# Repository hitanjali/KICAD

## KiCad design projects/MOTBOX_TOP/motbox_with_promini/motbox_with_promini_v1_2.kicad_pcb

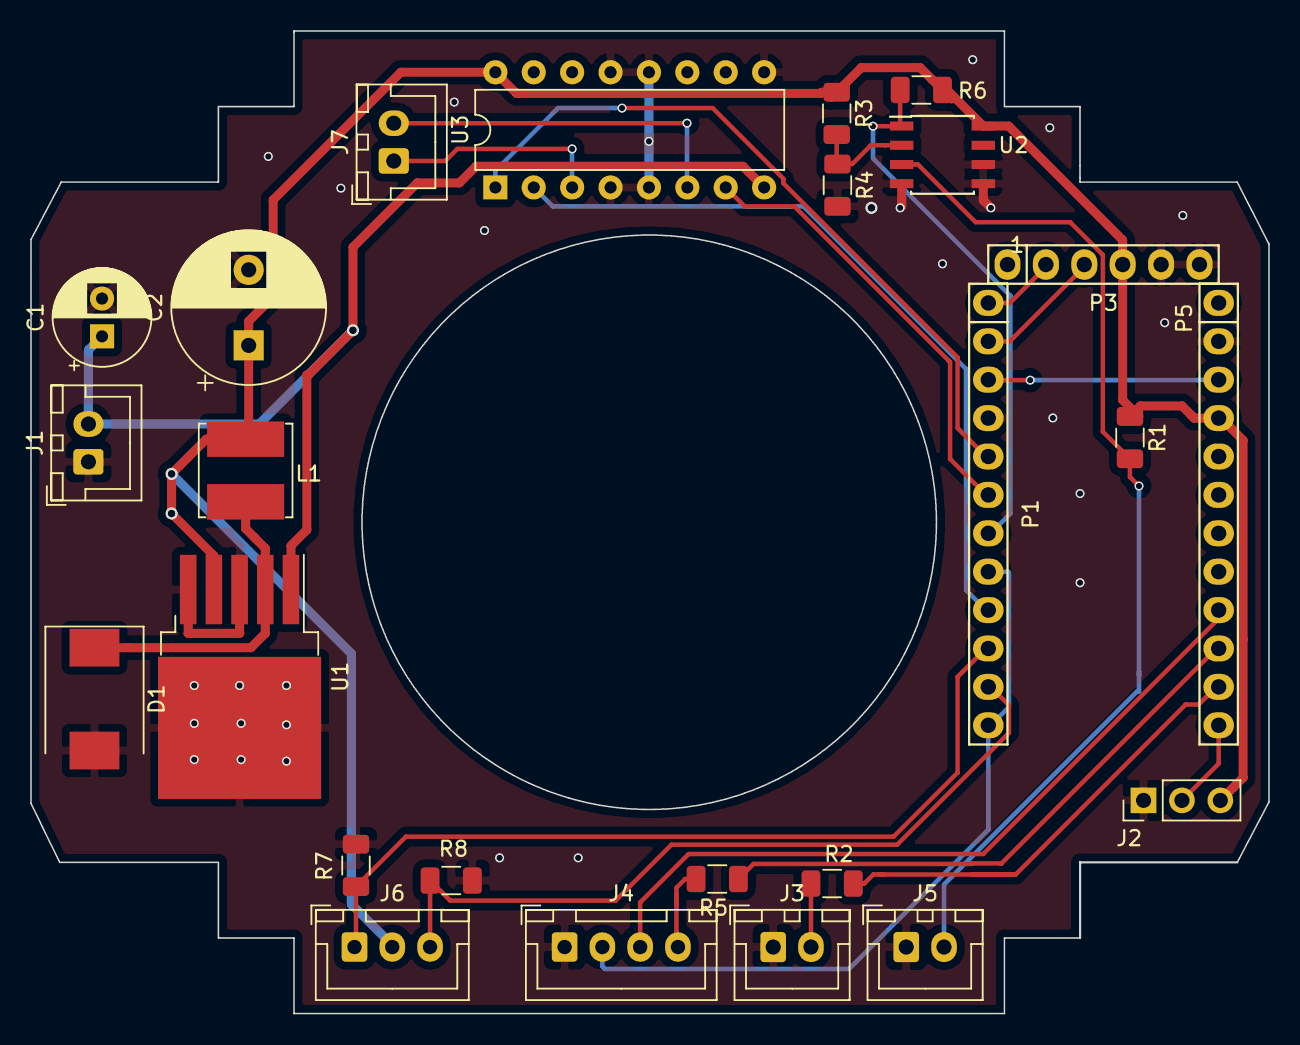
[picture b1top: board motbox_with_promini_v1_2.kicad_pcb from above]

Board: 2 copper layers, 81.9 x 65.0 mm, 25 parts (0 on the bottom side), 24 nets.

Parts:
C1: 100uF,25V; CP_Radial_D6.3mm_P2.50mm
C2: 1000uF,16V; CP_Radial_D10.0mm_P5.00mm
D1: SS34; D_SMC
J1, J3, J5, J7: JST_XH_2pin; JST_XH_B02B-XH-A_1x02_P2.50mm_Vertical
J2: Header_3pin_Male; PinHeader_1x03_P2.54mm_Vertical
J4: JST_XH_4pin; JST_XH_B04B-XH-A_1x04_P2.50mm_Vertical
J6: Conn_01x03; JST_XH_B03B-XH-A_1x03_P2.50mm_Vertical
L1: SRN6045-101M; L_Bourns_SRN6045TA
P1, P5: Female_Header_12pin; Socket_Strip_Arduino_1x12
P3: Female_Header_6pin; Socket_Strip_Arduino_1x06
R1: TBD; R_1206_3216Metric
R2, R5: 150; R_1206_3216Metric
R3, R4, R7, R8: 100K; R_1206_3216Metric
R6: 10K; R_1206_3216Metric
U1: LM2576R-5.0; TO-263-5_TabPin3
U2: LM393; SOIC-8_3.9x4.9mm_P1.27mm
U3: L293D; DIP-16_W7.62mm

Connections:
+5V: C2.1, J2.3, J6.2, L1.2, P3.4, P5.4, R1.1, R3.1, R6.1, U1.4, U2.8, U3.16
+12V: C1.1, J1.2, U1.1, U3.8
/0(Rx): P1.2, P3.3
/1(Tx): P1.1, P3.2
/2: P1.5, U3.1
/3: P1.6, U3.7
/4: P1.7, R6.2, U2.1
/5: J4.2, P1.8, P1.12
/6: P1.9, U3.2
/7: J6.1, P1.10, R7.1
/8: J6.3, P1.11, R8.1
/10: J2.2, P5.12
/11: P5.11, R2.1
/12: P5.10, R5.1
/13: J4.3, P5.9
/Reset: P1.3, P5.3
GND: C1.2, C2.2, D1.2, J1.1, J2.1, J3.1, J4.1, J5.1, P1.4, P3.5, P3.6, P5.2, R4.2, R7.2, R8.2, U1.3, U1.5, U2.4, U2.5, U2.6, U3.4, U3.5, U3.9, U3.12, U3.13
unnamed: D1.1, L1.1, U1.2
unnamed: J3.2, R2.2
unnamed: J4.4, R5.2
unnamed: J5.2, R1.2, U2.3
unnamed: J7.1, U3.3
unnamed: J7.2, U3.6
unnamed: R3.2, R4.1, U2.2

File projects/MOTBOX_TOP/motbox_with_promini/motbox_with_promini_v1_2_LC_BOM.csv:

S.No,Manufacturing Part No,Designator,Quantity,Description(VALUE),Package(CASE),Top/Bottom,Points (No. of Pins),Comments,,
1,  , "C1, " , "1" , "100uF,25V" , "Capacitor_THT:CP_Radial_D6.3mm_P2.50mm" , TOP , 2, "Polarized capacitor, small US symbol", , 
2,  , "C2, " , "1" , "1000uF,16V" , "Capacitor_THT:CP_Radial_D10.0mm_P5.00mm" , TOP , 2, "Polarized capacitor, small US symbol", , 
3,  , "D1, " , "1" , "SS34" , "Diode_SMD:D_SMC" , TOP , 2, "Schottky diode", , 
4,  , "J2, " , "1" , "Header_3pin_Male" , "Connector_PinHeader_2.54mm:PinHeader_1x03_P2.54mm_Vertical" , TOP , 3, "Generic connector, single row, 01x03, script generated (kicad-library-utils/schlib/autogen/connector/)", , 
5,  , "J4, " , "1" , "JST_XH_4pin" , "Connector_JST:JST_XH_B04B-XH-A_1x04_P2.50mm_Vertical" , TOP , 4, "Generic connector, single row, 01x04, script generated (kicad-library-utils/schlib/autogen/connector/)", , 
6,  , "J5, J7, J1, J3, " , "4" , "JST_XH_2pin" , "Connector_JST:JST_XH_B02B-XH-A_1x02_P2.50mm_Vertical" , TOP , 2, "Generic connector, single row, 01x02, script generated (kicad-library-utils/schlib/autogen/connector/)", , 
7,  , "J6, " , "1" , "JST_XH_3pin" , "Connector_JST:JST_XH_B03B-XH-A_1x03_P2.50mm_Vertical" , TOP , 3, "Generic connector, single row, 01x03, script generated (kicad-library-utils/schlib/autogen/connector/)", , 
8,  , "L1, " , "1" , "SRN6045-101M" , "Inductor_SMD:L_Bourns_SRN6045TA" , TOP , 2, "Inductor, small symbol", , 
9,  , "P1, P5, " , "2" , "Female_Header_12pin" , "Socket_Arduino_Pro_Mini:Socket_Strip_Arduino_1x12" , TOP , 12, "Generic connector, single row, 01x12, script generated (kicad-library-utils/schlib/autogen/connector/)", , 
10,  , "P3, " , "1" , "Female_Header_6pin" , "Socket_Arduino_Pro_Mini:Socket_Strip_Arduino_1x06" , TOP , 6, "Generic connector, single row, 01x06, script generated (kicad-library-utils/schlib/autogen/connector/)", , 
11,  , "R1, " , "1" , "60K" , "Resistor_SMD:R_1206_3216Metric" , TOP , 2, "Resistor, US symbol", , 
12,  , "R2, R5, " , "2" , "150R" , "Resistor_SMD:R_1206_3216Metric" , TOP , 2, "Resistor, US symbol", , 
13,  , "R3, R4, R8, R7, " , "4" , "100K" , "Resistor_SMD:R_1206_3216Metric" , TOP , 2, "Resistor, US symbol", , 
14,  , "R6, " , "1" , "10K" , "Resistor_SMD:R_1206_3216Metric" , TOP , 2, "Resistor, US symbol", , 
15,  , "U1, " , "1" , "LM2576R-5.0" , "Package_TO_SOT_SMD:TO-263-5_TabPin3" , TOP , 5, "12V, 3A SIMPLE SWITCHER® Step-Down Voltage Regulator, High Voltage Input, TO-263", , 
16,  , "U2, " , "1" , "LM393" , "Package_SO:SOIC-8_3.9x4.9mm_P1.27mm" , TOP , 8, "Low-Power, Low-Offset Voltage, Dual Comparators, DIP-8/SOIC-8/SSOP-8", , 
17,  , "U3, " , "1" , "L293D" , "Package_DIP:DIP-16_W7.62mm" , TOP , 16, "Quadruple Half-H Drivers", ,

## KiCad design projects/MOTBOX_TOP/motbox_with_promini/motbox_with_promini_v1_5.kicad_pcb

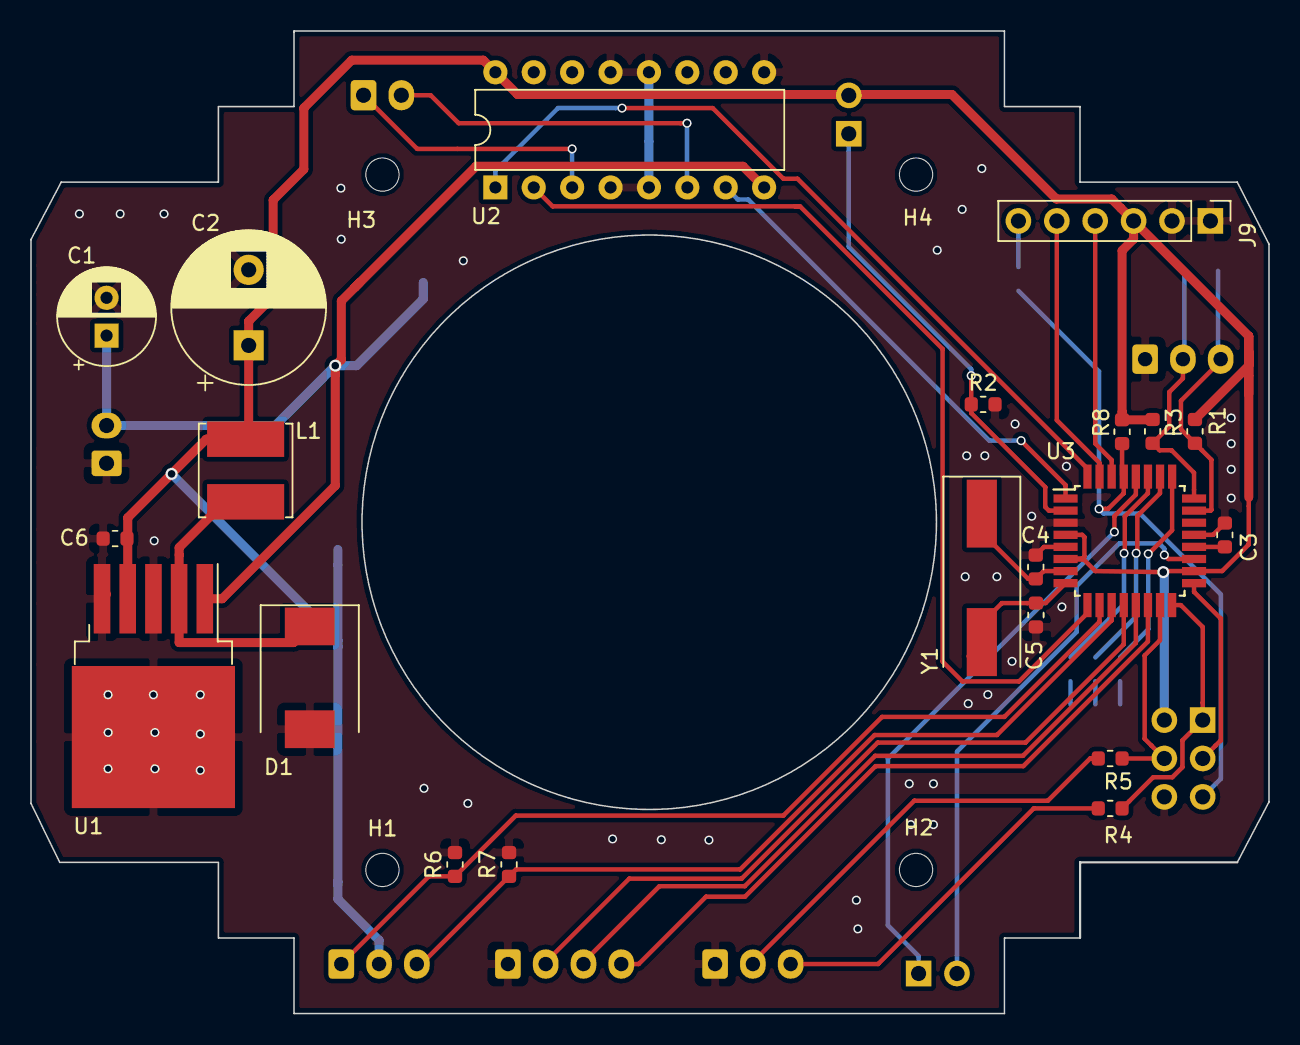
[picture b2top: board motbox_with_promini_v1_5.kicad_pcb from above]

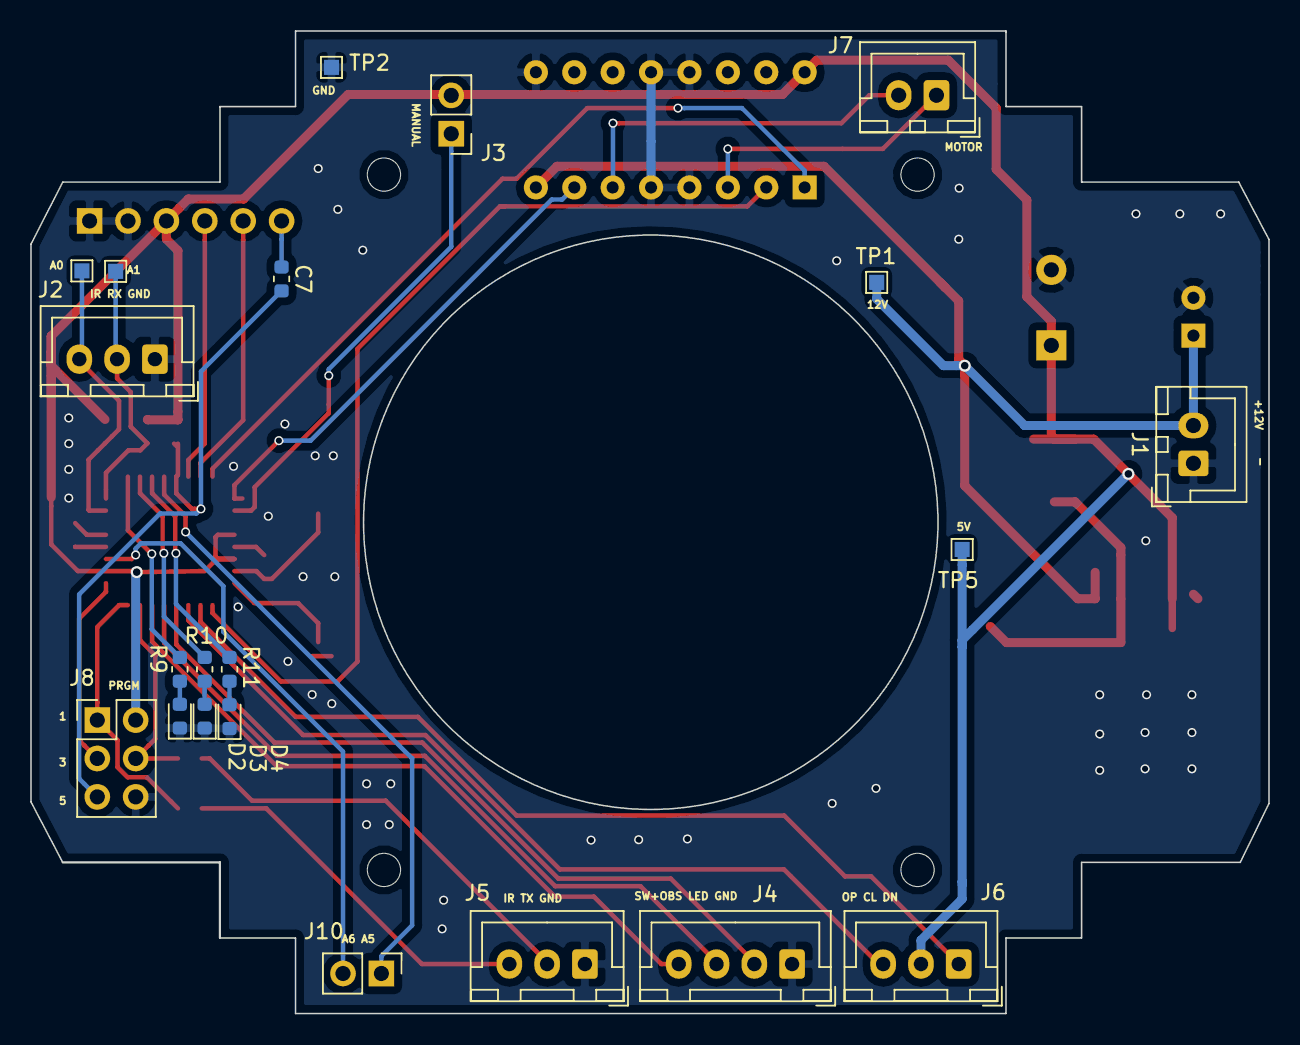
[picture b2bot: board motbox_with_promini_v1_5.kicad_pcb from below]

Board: 2 copper layers, 81.9 x 65.0 mm, 46 parts (21 on the bottom side), 37 nets.

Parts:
C1: 100uF,25V; CP_Radial_D6.3mm_P2.50mm
C2: 1000uF,16V; CP_Radial_D10.0mm_P5.00mm
C3, C6, C7: 0.1uF; C_0603_1608Metric
C4, C5: 22pF; C_0603_1608Metric
D1: SS34; D_SMC
D2, D3, D4: LED_Small; D_0603_1608Metric
H1, H2, H3, H4: MountingHole; MountingHole_2.2mm_M2_ISO7380
J1, J7: JST_XH_2pin; JST_XH_B02B-XH-A_1x02_P2.50mm_Vertical
J2, J5, J6: JST_XH_3pin; JST_XH_B03B-XH-A_1x03_P2.50mm_Vertical
J3, J10: Conn_01x02; PinHeader_1x02_P2.54mm_Vertical
J4: JST_XH_4pin; JST_XH_B04B-XH-A_1x04_P2.50mm_Vertical
J8: Conn_02x03_Odd_Even; PinHeader_2x03_P2.54mm_Vertical
J9: Conn_01x06; PinHeader_1x06_P2.54mm_Vertical
L1: SRN6045-101M; L_Bourns_SRN6045TA
R1, R3: 60K; R_0603_1608Metric
R2, R6, R7: 100K; R_0603_1608Metric
R4, R5, R9, R10, R11: 150E; R_0603_1608Metric
R8: 10K; R_0603_1608Metric
TP1, TP2, TP3, TP4, TP5: TestPoint; TestPoint_Pad_1.0x1.0mm
U1: LM2576R-5.0; TO-263-5_TabPin3
U2: L293D; DIP-16_W7.62mm
U3: ATmega328P-AU; TQFP-32_7x7mm_P0.8mm
Y1: ABLS-16.000MHZ-B4-T; Crystal_SMD_HC49-SD

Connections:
+5V: C2.1, C6.2, J3.2, J6.2, J8.2, J9.3, L1.2, R1.1, R3.1, R8.1, TP5.1, U1.4, U2.16, U3.4, U3.6, U3.18
+12V: C1.1, J1.2, TP1.1, U1.1, U2.8
/2: U2.1, U3.32
/3: U2.7, U3.1
/4: J3.1, R2.1, U3.2
/5: U2.2, U3.9
/6: J6.1, R6.1, U3.10
/7: J6.3, R7.1, U3.11
/8: J4.2, U3.12
/9: J4.3, U3.13
/10: J4.4, U3.14
/11: J8.4, R5.1, U3.15
/12: J8.1, R4.1, U3.16
/A0: J2.3, R1.2, TP3.1, U3.23
/A1: J2.2, R3.2, TP4.1, U3.24
/Arduino_pro_mini/A2: R9.2, U3.25
/Arduino_pro_mini/A3: R10.2, U3.26
/Arduino_pro_mini/A4: R11.2, U3.27
/Arduino_pro_mini/A5: J10.1, U3.28
/Arduino_pro_mini/A6: J10.2, U3.19
/Arduino_pro_mini/DTR: C7.1, J9.6
/Arduino_pro_mini/RESET: C7.2, J8.5, R8.2, U3.29
/Arduino_pro_mini/RX: J9.4, U3.30
/Arduino_pro_mini/SCK: J8.3, U3.17
/Arduino_pro_mini/TX: J9.5, U3.31
GND: C1.2, C2.2, C3.2, C4.1, C5.1, C6.1, D1.2, D2.1, D3.1, D4.1, J1.1, J2.1, J4.1, J5.1, J8.6, J9.1, J9.2, R2.2, R6.2, R7.2, TP2.1, U1.3, U1.5, U2.4, U2.5, U2.9, U2.12, U2.13, U3.3, U3.5, U3.21
unnamed: C3.1, U3.20
unnamed: C4.2, U3.7, Y1.1
unnamed: C5.2, U3.8, Y1.2
unnamed: D1.1, L1.1, U1.2
unnamed: D2.2, R9.1
unnamed: D3.2, R10.1
unnamed: D4.2, R11.1
unnamed: J5.2, R5.2
unnamed: J5.3, R4.2
unnamed: J7.1, U2.3
unnamed: J7.2, U2.6
